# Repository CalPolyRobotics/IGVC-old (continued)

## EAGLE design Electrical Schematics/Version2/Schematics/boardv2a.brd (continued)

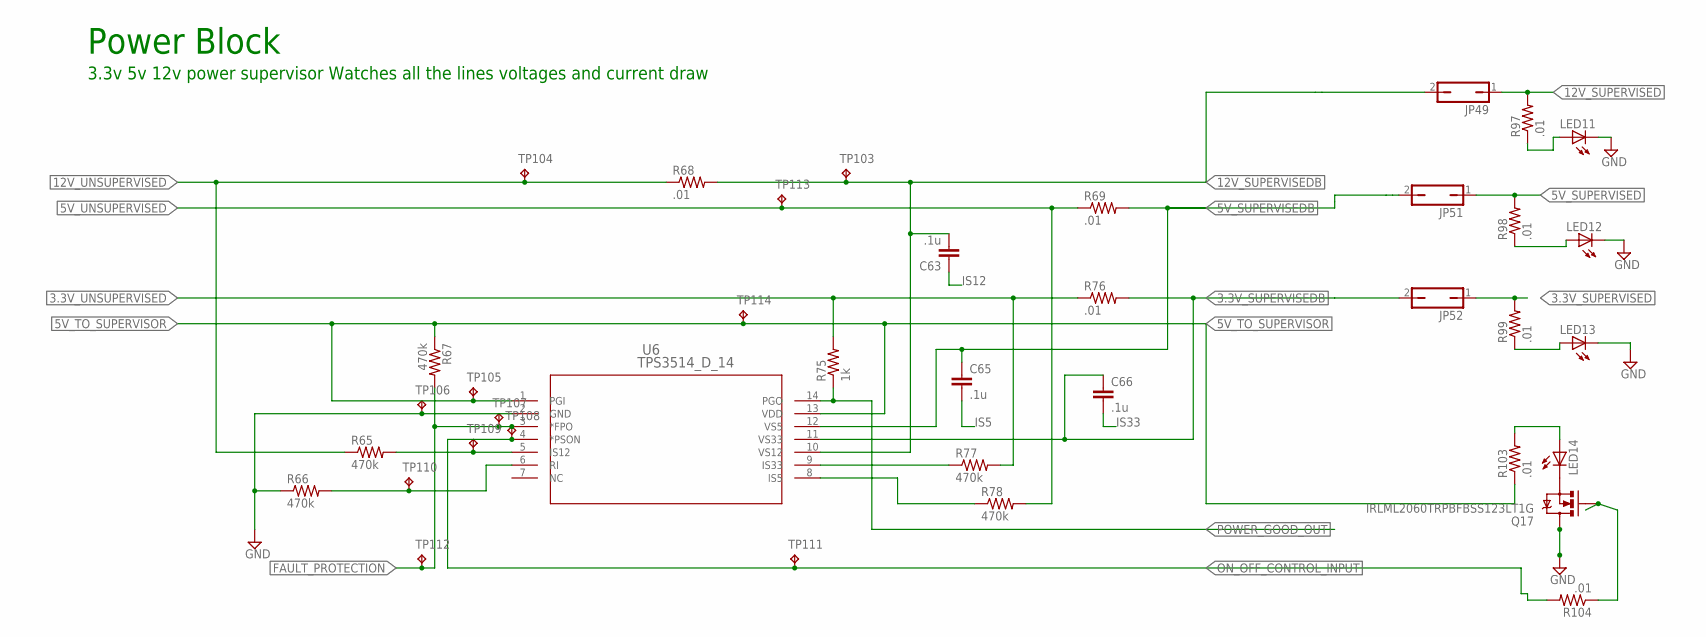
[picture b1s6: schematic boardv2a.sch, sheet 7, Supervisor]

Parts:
C63, C65, C66: .1u; C0603
JP49, JP51, JP52: JP1Q; JP1
LED11, LED12, LED13, LED14: LEDSML1206; SML1206
Q17: IRLML2060TRPBFBSS123LT1G; SOT23-3
R65, R66, R67, R77, R78: 470k; 0603-RES
R68, R69, R76, R97, R98, R99, R103, R104: .01; 0603-RES
R75: 1k; 0603-RES
TP103, TP105, TP106, TP107, TP108, TP109, TP110, TP111, TP112, TP113, TP114: TPB1,27; B1,27
TP104: TPTP06R; TP06R
U6: TPS3514_D_14; D14

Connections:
3.3V_SUPERVISED: JP52.1, R99.2; also elsewhere on the board
3.3V_SUPERVISEDB: C66.1, JP52.2, R76.2, U6.11 (VS33)
3.3V_UNSUPERVISED: R75.2, R76.1, R77.2; also elsewhere on the board
5V_SUPERVISED: JP51.1, R98.2; also elsewhere on the board
5V_SUPERVISEDB: C65.1, JP51.2, R69.2, U6.12 (VS5)
5V_TO_SUPERVISOR: R67.1, R103.1, TP105.TP, TP114.TP, U6.1 (PGI), U6.13 (VDD); also elsewhere on the board
5V_UNSUPERVISED: R69.1, R78.2, TP113.TP; also elsewhere on the board
12V_SUPERVISED: JP49.1, R97.2; also elsewhere on the board
12V_SUPERVISEDB: C63.2, JP49.2, R68.2, TP103.TP, U6.10 (VS12)
12V_UNSUPERVISED: R65.1, R68.1, TP104.TP; also elsewhere on the board
FAULT_PROTECTION: R67.2, TP107.TP, TP112.TP, U6.3 (*FPO)
GND: LED11.C, LED12.C, LED13.C, Q17.3 (D), R66.1, TP106.TP, U6.2 (GND); also elsewhere on the board
IS5: C65.2, R78.1, U6.8 (IS5)
IS12: C63.1, R65.2, TP109.TP, U6.5 (IS12)
IS33: C66.2, R77.1, U6.9 (IS33)
unnamed: LED14.C, Q17.2 (S)
unnamed: R66.2, TP110.TP, U6.6 (RI)
unnamed: LED13.A, R99.1
unnamed: LED12.A, R98.1
unnamed: LED11.A, R97.1
unnamed: LED14.A, R103.2
unnamed: Q17.1 (G), R104.1
ON_OFF_CONTROL_INPUT: R104.2, TP108.TP, TP111.TP, U6.4 (*PSON)
POWER_GOOD_OUT: R75.1, U6.14 (PGO); also elsewhere on the board

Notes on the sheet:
Power Block
3.3v 5v 12v power supervisor Watches all the lines voltages and current draw

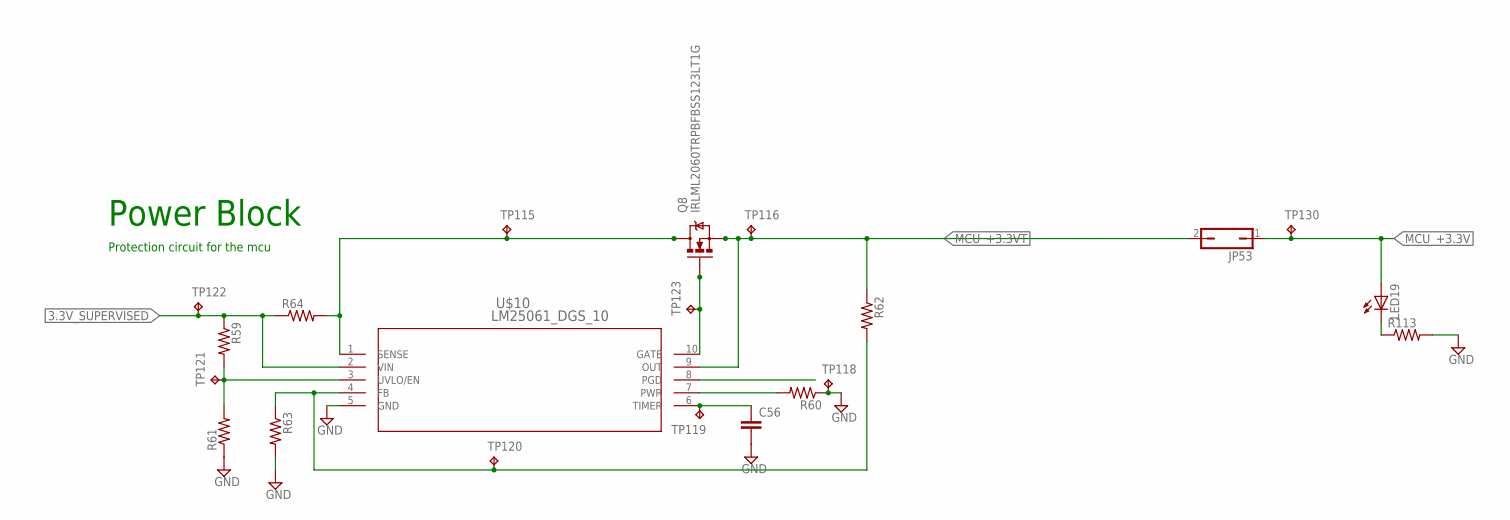
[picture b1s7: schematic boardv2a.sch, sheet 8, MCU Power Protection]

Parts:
C56: CC0603; C0603
JP53: JP1Q; JP1
LED19: LEDSML1206; SML1206
Q8: IRLML2060TRPBFBSS123LT1G; SOT23-3
R59, R60, R61, R62, R63, R64, R113: RESISTOR0603-RES; 0603-RES
TP115, TP116, TP118, TP119, TP120, TP121, TP122, TP123, TP130: TPB1,27; B1,27
U$10: LM25061_DGS_10; MUB10A

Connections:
3.3V_SUPERVISED: R59.1, R64.1, TP122.TP, U$10.2 (VIN); also elsewhere on the board
GND: C56.2, R60.1, R61.1, R63.2, R113.2, TP118.TP, U$10.5 (GND); also elsewhere on the board
MCU_+3.3V: JP53.1, LED19.A, TP130.TP; also elsewhere on the board
MCU_+3.3VT: JP53.2, Q8.2 (S), R62.1, TP116.TP, U$10.9 (OUT)
unnamed: C56.1, TP119.TP, U$10.6 (TIMER)
unnamed: R60.2, U$10.7 (PWR)
unnamed: R59.2, R61.2, TP121.TP, U$10.3 (UVLO/EN)
unnamed: Q8.3 (D), R64.2, TP115.TP, U$10.1 (SENSE)
unnamed: Q8.1 (G), TP123.TP, U$10.10 (GATE)
unnamed: R62.2, R63.1, TP120.TP, U$10.4 (FB)
unnamed: LED19.C, R113.1

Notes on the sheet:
Power Block
Protection circuit for the mcu

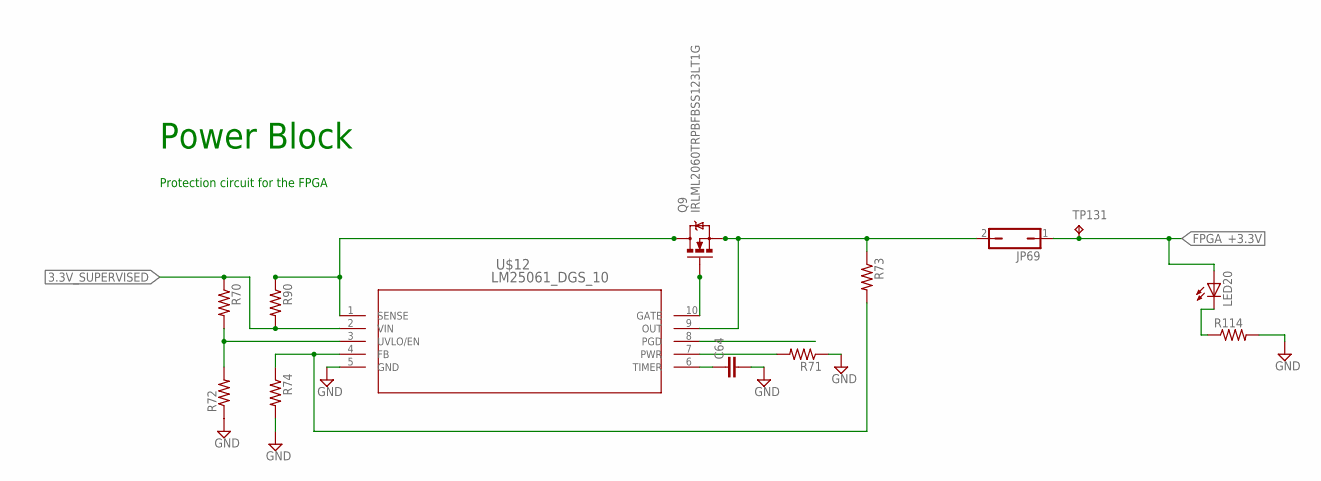
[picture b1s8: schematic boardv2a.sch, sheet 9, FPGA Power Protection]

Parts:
C64: CC0603; C0603
JP69: JP1Q; JP1
LED20: LEDSML1206; SML1206
Q9: IRLML2060TRPBFBSS123LT1G; SOT23-3
R70, R71, R72, R73, R74, R90, R114: RESISTOR0603-RES; 0603-RES
TP131: TPB1,27; B1,27
U$12: LM25061_DGS_10; MUB10A

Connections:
3.3V_SUPERVISED: R70.1, R90.2, U$12.2 (VIN); also elsewhere on the board
FPGA_+3.3V: JP69.1, LED20.A, TP131.TP
GND: C64.2, R71.1, R72.1, R74.2, R114.2, U$12.5 (GND); also elsewhere on the board
unnamed: C64.1, U$12.6 (TIMER)
unnamed: R71.2, U$12.7 (PWR)
unnamed: R70.2, R72.2, U$12.3 (UVLO/EN)
unnamed: Q9.3 (D), R90.1, U$12.1 (SENSE)
unnamed: Q9.1 (G), U$12.10 (GATE)
unnamed: R73.2, R74.1, U$12.4 (FB)
unnamed: JP69.2, Q9.2 (S), R73.1, U$12.9 (OUT)
unnamed: LED20.C, R114.1

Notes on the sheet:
Power Block
Protection circuit for the FPGA

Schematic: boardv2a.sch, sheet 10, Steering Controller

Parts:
R2401, R2402, R2403, R2404, R2405: 1k; R0603
SV2: FE05-1

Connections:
MCU_STEERCTRL_DIAGA: R2403.1; also elsewhere on the board
MCU_STEERCTRL_DIAGB: R2404.1; also elsewhere on the board
MCU_STEERCTRL_INA: R2401.1; also elsewhere on the board
MCU_STEERCTRL_INB: R2402.1; also elsewhere on the board
MCU_STEERCTRL_PWM: R2405.1; also elsewhere on the board
unnamed: R2404.2, SV2.4
unnamed: R2402.2, SV2.2
unnamed: R2403.2, SV2.3
unnamed: R2405.2, SV2.5

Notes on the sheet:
Steering Controller

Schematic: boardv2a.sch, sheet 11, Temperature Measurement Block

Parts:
JP97, JP98, JP99, JP100, JP101, JP102: JP2E; JP2

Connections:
3.3V_TEMP_PWR: JP97.2, JP98.2, JP99.2, JP100.2, JP101.2, JP102.2
MCU_A_GND: JP97.3, JP98.3, JP99.3, JP100.3, JP101.3, JP102.3; also elsewhere on the board
MCU_TEMPB_A1: JP98.1; also elsewhere on the board
MCU_TEMPC_A2: JP99.1; also elsewhere on the board
MCU_TEMPD_A3: JP100.1; also elsewhere on the board
MCU_TEMPE_A4: JP101.1; also elsewhere on the board
MCU_TEMPF_A5: JP102.1; also elsewhere on the board
MCU_TEMP_A0: JP97.1; also elsewhere on the board

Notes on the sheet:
motorcontroler
regular 3.3 temp
regulator 5v temp
regulator 12v temp
motor temp
ESC temp
Tempature Measurement Block

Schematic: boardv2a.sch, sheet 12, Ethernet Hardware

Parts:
C16, C70, C71: 0.1uF; C0603
C72, C73: 18pf; C0603
C74, C75, C77, C78, C79, C80, C81, C82, C83, C84, C85, C109, C110, C111: 0.1uf; C0603
C76: 0.1; C0603
C106: 3.3uf; C0603
C107, C108: 10uf; C0603
JP48: JP1E; JP1
L3, L4: BLM15HB121SN1; 0402
LED10: LEDSML1206; SML1206
R28: 1k; 0603-RES
R30: 10k; 0603-RES
R82, R83, R86, R87: 51; 0603-RES
R84, R85: 200; 0603-RES
R88: 16; 0603-RES
R89: 300; 0603-RES
R94: 560ohms; 0603-RES
U8: W5100; LQFP-80
U$21: 7A-16.000MAAJ-T; 2-SMD
U$22: ETHERNET_CONNECTOR; RB1-125BAG1A

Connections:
0.1: R83.2, U8.8 (TXOP), U$22.R1
1V8A: C84.1, C85.1, C108.1, L3.2, U8.7 (1V8A), U8.74 (1V8A)
1V8D: C106.1, C107.1, L3.1
3.3V_SUPERVISED: JP48.1; also elsewhere on the board
3V3A: C110.1, C111.1, L4.1, U8.2 (3V3A)
ETHERNET_3.3_J_+: C16.1, C74.1, C75.1, C76.1, C77.1, C78.1, C79.1, C109.1, JP48.2, L4.2, LED10.A, R28.1, R84.2, R85.2, U8.12 (3V3D), U8.18 (3V3D), U8.44 (3V3D), U$22.R3
ETHERNET_MCU_INT: R30.2, U8.56 (*INT); also elsewhere on the board
GND: C16.2, C70.2, C71.2, C72.2, C73.2, C74.2, C75.2, C76.2, C77.2, C78.2, C79.2, C80.2, C81.2, C82.2, C83.2, C106.2, C107.2, C109.2, R30.1, R89.1, R94.1; also elsewhere on the board
GNDA: C84.2, C85.2, C108.2, C110.2, C111.2, U8.4 (GNDA), U8.10 (GNDA), U8.77 (GNDA)
MCU_ETHERNET_MISO: U8.27 (MISO); also elsewhere on the board
MCU_ETHERNET_MOSI: U8.28 (MOSI); also elsewhere on the board
MCU_ETHERNET_SCLK: U8.30 (SCLK); also elsewhere on the board
MCU_ETHERNET_SCS: U8.29 (*SCS); also elsewhere on the board
MCU_ETHERNET_SEN: R28.2, U8.31 (SEN)
unnamed: C71.1, R82.2, R83.1
unnamed: C70.1, R86.1, R87.2
unnamed: R82.1, U8.9 (TXON), U$22.R2
unnamed: R84.1, U$22.L1
unnamed: R85.1, U$22.L3
unnamed: R87.1, U8.6 (RXIN), U$22.R7
unnamed: R86.2, U8.5 (RXIP), U$22.R8
unnamed: U8.66 (LINKLED), U$22.L2
unnamed: U8.70 (FDXLED), U$22.L4
unnamed: LED10.C, R94.2
unnamed: C80.1, C81.1, C82.1, C83.1, U8.11 (1V8OUT), U8.15 (1V8D), U8.16 (1V8D), U8.33 (1V8D), U8.69 (1V8D)
unnamed: R88.1, R89.2
unnamed: R88.2, U8.1 (RSET_BG)
P$1_CLK_TO_XTLN_WIZNET: C72.1, U8.75 (XTLN), U$21.P$1
P$2_CLK_TO_XTLP_WIZNET: C73.1, U8.76 (XTLP), U$21.P$2
WIZNET_TO_GND: U8.13 (GNDD), U8.14 (GNDD), U8.17 (GNDD), U8.32 (GNDD), U8.34 (TEST3), U8.35 (TEST2), U8.36 (TEST1), U8.37 (TEST0), U8.43 (GNDD), U8.63 (OPMODE0), U8.64 (OPMODE1), U8.65 (OPMODE2), U8.68 (GNDD)

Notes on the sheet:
Ethernet Hardware Block

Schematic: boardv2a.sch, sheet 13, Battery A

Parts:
C1: 47nF; C0603
C2: 220nF; C0603
C3: 1uF; C0603
C4: 220pf; C0603
C5: 4.7UF; C0603
J1: JU05
JP3, JP21, JP28: JP1E; JP1
JP22: JP2E; JP2
LED8: LEDSML1206; SML1206
R1: 2.2KOHM; 0603-RES
R2: 100UOHMS; 0603-RES
R9, R10: 500ohm; 0603-RES
R12: 3.3k; 0603-RES
R92: 560ohms; 0603-RES
SV3: MA03-2
U$1: MM912_637D1; QFN48
X1: KK-156-2

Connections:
5V_SUPERVISED: C5.1, JP21.1; also elsewhere on the board
BKGND: R12.1, SV3.6, U$1.47 (BKGD/MODC)
CON_MONA_+: JP3.1; also elsewhere on the board
CON_MONA_+_J: JP3.2, LED8.A, R1.2
CON_MONA_-: C2.2, C3.2, JP22.1, R2.2, R9.2, U$1.11 (VSSRX), U$1.13 (VSSD2D), U$1.18 (DGND); also elsewhere on the board
CON_MONB_+: R2.1, R10.2; also elsewhere on the board
GND: C4.2, C5.2, JP22.3, R92.1, SV3.5, U$1.4 (TEST), U$1.16 (GNDSUB), U$1.20 (GNDSUB1), U$1.30 (GNDSUB2), U$1.41 (GNDSUB3), U$1.44 (DGND1); also elsewhere on the board
MCU_BATMON_LIN: U$1.22 (LIN); also elsewhere on the board
MCU_BATMON_LINGND: U$1.23 (LGND); also elsewhere on the board
MCU_IO_RALAYA: U$1.6 (PA4); also elsewhere on the board
MONA_AGND: C1.2, JP22.2, U$1.27 (AGND), U$1.33 (ADCGND)
unnamed: R1.1, U$1.34 (VSENSE)
unnamed: J1.5, U$1.10 (PA0/MISO)
unnamed: J1.4, U$1.9 (PA1/MOSI)
unnamed: J1.3, U$1.8 (PA2/SCK)
unnamed: J1.2, U$1.7 (PA3/*SS)
unnamed: C4.1, U$1.29 (TSUP), X1.1
unnamed: U$1.28 (VTEMP), X1.2
unnamed: JP28.2, SV3.3, U$1.46 (*RESET)
unnamed: C3.1, U$1.14 (VDDD2D), U$1.19 (VDDH)
unnamed: JP28.1, U$1.45 (*RESET_A)
unnamed: R10.1, U$1.32 (ISENSEH)
unnamed: R9.1, U$1.31 (ISENSEL)
unnamed: C1.1, U$1.26 (VDDA)
unnamed: LED8.C, R92.2
VDDX: C2.1, R12.2, SV3.1, U$1.12 (VDDRX), U$1.17 (VDDX)
VSUP: JP21.2, U$1.21 (VSUP)

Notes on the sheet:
Battery Monitoring Block A
TEMP CONNECTOR

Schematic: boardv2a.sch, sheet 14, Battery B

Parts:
C6: 47nF; C0603
C7: 220nF; C0603
C8: 1uF; C0603
C9: 4.7UF; C0603
C10: 220pf; C0603
J2: JU05
JP2, JP23, JP29: JP1E; JP1
JP24: JP2E; JP2
LED7: LEDSML1206; SML1206
R3: 2.2KOHM; 0603-RES
R4: 100UOHMS; 0603-RES
R5, R6: 500ohm; 0603-RES
R22: 3.3k; 0603-RES
R36: 560ohms; 0603-RES
SV4: MA03-2
U$2: MM912_637D1; QFN48
X2: KK-156-2

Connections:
5V_SUPERVISED: C9.1, JP23.1; also elsewhere on the board
5V_SUP_J1: JP23.2, U$2.21 (VSUP)
BKGNDB: R22.1, SV4.6
CON_MONB_+: JP2.1; also elsewhere on the board
CON_MONB_+_J: JP2.2, LED7.A, R3.2
CON_MONB_-: C7.2, C8.2, JP24.1, R4.2, R5.2, U$2.11 (VSSRX), U$2.13 (VSSD2D), U$2.18 (DGND); also elsewhere on the board
CON_MONC_+: R4.1, R6.2; also elsewhere on the board
GND: C9.2, C10.2, JP24.3, R36.1, SV4.5, U$2.4 (TEST), U$2.16 (GNDSUB), U$2.20 (GNDSUB1), U$2.30 (GNDSUB2), U$2.41 (GNDSUB3), U$2.44 (DGND1); also elsewhere on the board
MCU_BATMON_LIN: U$2.22 (LIN); also elsewhere on the board
MCU_BATMON_LINGND: U$2.23 (LGND); also elsewhere on the board
MCU_IO_RALAYB: U$2.6 (PA4); also elsewhere on the board
MONB_AGND: C6.2, JP24.2, U$2.27 (AGND), U$2.33 (ADCGND)
unnamed: J2.5, U$2.10 (PA0/MISO)
unnamed: JP29.1, U$2.45 (*RESET_A)
unnamed: J2.4, U$2.9 (PA1/MOSI)
unnamed: J2.3, U$2.8 (PA2/SCK)
unnamed: J2.2, U$2.7 (PA3/*SS)
unnamed: R3.1, U$2.34 (VSENSE)
unnamed: C10.1, U$2.29 (TSUP), X2.1
unnamed: U$2.28 (VTEMP), X2.2
unnamed: JP29.2, SV4.3, U$2.46 (*RESET)
unnamed: R6.1, U$2.32 (ISENSEH)
unnamed: C6.1, U$2.26 (VDDA)
unnamed: R5.1, U$2.31 (ISENSEL)
unnamed: C8.1, U$2.14 (VDDD2D), U$2.19 (VDDH)
unnamed: LED7.C, R36.2
VDDXB: C7.1, R22.2, SV4.1, U$2.12 (VDDRX), U$2.17 (VDDX)

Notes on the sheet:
Battery Monitor B
TEMP CONNECTOR

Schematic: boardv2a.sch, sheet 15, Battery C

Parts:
C11: 47nF; C0603
C12: 220nF; C0603
C13: 1uF; C0603
C14: 4.7UF; C0603
C15: 220pf; C0603
J3: JU05
JP1, JP25, JP30: JP1E; JP1
JP26: JP2E; JP2
LED6: LEDSML1206; SML1206
R7: 2.2KOHM; 0603-RES
R8: 100UOHMS; 0603-RES
R23: 3.3k; 0603-RES
R37, R38: 500ohm; 0603-RES
R39: 560ohms; 0603-RES
SV5: MA03-2
U$3: MM912_637D1; QFN48
X3: KK-156-2

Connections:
5V_SUPERVISED: C14.1, JP25.1; also elsewhere on the board
5V_SU_J: JP25.2, U$3.21 (VSUP)
BKGNDC: R23.1, SV5.6
CON_MONC_+: JP1.1; also elsewhere on the board
CON_MONC_+_J: JP1.2, LED6.A, R7.2
CON_MONC_-: C12.2, C13.2, JP26.1, R8.2, R37.2, U$3.11 (VSSRX), U$3.13 (VSSD2D), U$3.18 (DGND); also elsewhere on the board
CON_MONC_SP: R8.1, R38.2; also elsewhere on the board
GND: C14.2, C15.2, JP26.3, R39.1, SV5.5, U$3.4 (TEST), U$3.16 (GNDSUB), U$3.20 (GNDSUB1), U$3.30 (GNDSUB2), U$3.41 (GNDSUB3), U$3.44 (DGND1); also elsewhere on the board
MCU_BATMON_LIN: U$3.22 (LIN); also elsewhere on the board
MCU_BATMON_LINGND: U$3.23 (LGND); also elsewhere on the board
MCU_IO_RALAYC: U$3.6 (PA4); also elsewhere on the board
MONC_AGND: C11.2, JP26.2, U$3.27 (AGND), U$3.33 (ADCGND)
unnamed: JP30.2, SV5.3, U$3.46 (*RESET)
unnamed: JP30.1, U$3.45 (*RESET_A)
unnamed: J3.5, U$3.10 (PA0/MISO)
unnamed: J3.4, U$3.9 (PA1/MOSI)
unnamed: J3.3, U$3.8 (PA2/SCK)
unnamed: J3.2, U$3.7 (PA3/*SS)
unnamed: R7.1, U$3.34 (VSENSE)
unnamed: C12.1, U$3.12 (VDDRX), U$3.17 (VDDX)
unnamed: C15.1, U$3.29 (TSUP), X3.1
unnamed: U$3.28 (VTEMP), X3.2
unnamed: R38.1, U$3.32 (ISENSEH)
unnamed: C11.1, U$3.26 (VDDA)
unnamed: R37.1, U$3.31 (ISENSEL)
unnamed: LED6.C, R39.2
VDDXC: C13.1, R23.2, SV5.1, U$3.14 (VDDD2D), U$3.19 (VDDH)

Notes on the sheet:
Battery Monitoring Block C
TEMP CONNECTOR

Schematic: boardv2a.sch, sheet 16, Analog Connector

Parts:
JP111: JP2E; JP2

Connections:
MCU_+3.3V: JP111.3; also elsewhere on the board
MCU_A_GND: JP111.1; also elsewhere on the board
MCU_STEERING_POT: JP111.2; also elsewhere on the board

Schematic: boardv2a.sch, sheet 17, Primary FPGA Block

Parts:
C21, C22, C23, C25, C26, C27, C28, C88: 10uF; 0603-CAP
C24, C29, C30, C31, C32, C33, C34, C35, C36, C37, C89: 1uF; 0603-CAP
L7: BLM15HB121SN1; 0402
Q7: ASFL1; ASF
R33: 10k; 0603-RES
U$6: XC6SLX4-2TQG144C; TQ144
U$11: 1.2VREG; SOT-223

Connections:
128MHZCLK_OUT_TO_GCLK_FPGA: Q7.3 (FO), U$6.P56 (IO_L30P_GCLK1_D13_2)
CONGND: L7.2; also elsewhere on the board
FPGA_CMPCS_B_2: U$6.P72 (CMPCS_B_2)
FPGA_DONE_2: U$6.P71 (DONE_2)
FPGA_L1N_1: U$6.P104 (IO_L1N_VREF_1); also elsewhere on the board
FPGA_L1N_2: U$6.P69 (IO_L1N_M0_CMPMISO_2); also elsewhere on the board
FPGA_L1N_3_MODULEF_ISOLATOR: U$6.P34 (IO_L1N_VREF_3); also elsewhere on the board
FPGA_L1P_1: U$6.P105 (IO_L1P_1); also elsewhere on the board
FPGA_L1P_2: U$6.P70 (IO_L1P_CCLK_2); also elsewhere on the board
FPGA_L1P_3_MODULEF_ISOLATOR: U$6.P35 (IO_L1P_3); also elsewhere on the board
FPGA_L2N_2: U$6.P66 (IO_L2N_CMPMOSI_2); also elsewhere on the board
FPGA_L2N_3: U$6.P32 (IO_L2N_3); also elsewhere on the board
FPGA_L2P_2: U$6.P67 (IO_L2P_CMPCLK_2); also elsewhere on the board
FPGA_L2P_3: U$6.P33 (IO_L2P_3); also elsewhere on the board
FPGA_L3N_0: U$6.P139 (IO_L3N_0); also elsewhere on the board
FPGA_L3N_2: U$6.P64 (IO_L3N_MOSI_CSI_B_MISO0_2); also elsewhere on the board
FPGA_L3P_0: U$6.P140 (IO_L3P_0); also elsewhere on the board
FPGA_L3P_2: U$6.P65 (IO_L3P_D0_DIN_MISO_MISO1_2); also elsewhere on the board
FPGA_L12N_2: U$6.P61 (IO_L12N_D2_MISO3_2); also elsewhere on the board
FPGA_L12P_2: U$6.P62 (IO_L12P_D1_MISO2_2); also elsewhere on the board
FPGA_L13N_2: U$6.P59 (IO_L13N_D10_2); also elsewhere on the board
FPGA_L13P_2: U$6.P60 (IO_L13P_M1_2); also elsewhere on the board
FPGA_L14N_2_MODULEG_ISOLATOR: U$6.P57 (IO_L14N_D12_2); also elsewhere on the board
FPGA_L14P_2_MODULEG_ISOLATOR: U$6.P58 (IO_L14P_D11_2); also elsewhere on the board
FPGA_L30N_2: U$6.P55 (IO_L30N_GCLK0_USERCCLK_2); also elsewhere on the board
FPGA_L31N_2: U$6.P50 (IO_L31N_GCLK30_D15_2); also elsewhere on the board
FPGA_L31P_2: U$6.P51 (IO_L31P_GCLK31_D14_2); also elsewhere on the board
FPGA_L32N_1: U$6.P101 (IO_L32N_1); also elsewhere on the board
FPGA_L32P_1: U$6.P102 (IO_L32P_1); also elsewhere on the board
FPGA_L33N_1: U$6.P99 (IO_L33N_1); also elsewhere on the board
FPGA_L33P_1: U$6.P100 (IO_L33P_1); also elsewhere on the board
FPGA_L34N_1: U$6.P97 (IO_L34N_1); also elsewhere on the board
FPGA_L34P_1: U$6.P98 (IO_L34P_1); also elsewhere on the board
FPGA_L36N_3_MODULEC_ISOLATOR: U$6.P29 (IO_L36N_3); also elsewhere on the board
FPGA_L36P_3_MODULEC_ISOLATOR: U$6.P30 (IO_L36P_3); also elsewhere on the board
FPGA_L37N_3: U$6.P26 (IO_L37N_3); also elsewhere on the board
FPGA_L37P_3: U$6.P27 (IO_L37P_3); also elsewhere on the board
FPGA_L40N_1: U$6.P94 (IO_L40N_GCLK10_1); also elsewhere on the board
FPGA_L40P_1: U$6.P95 (IO_L40P_GCLK11_1); also elsewhere on the board
FPGA_L41N_1: U$6.P92 (IO_L41N_GCLK8_1); also elsewhere on the board
FPGA_L41N_3: U$6.P23 (IO_L41N_GCLK26_3); also elsewhere on the board
FPGA_L41P_1: U$6.P93 (IO_L41P_GCLK9_IRDY1_1); also elsewhere on the board
FPGA_L41P_3: U$6.P24 (IO_L41P_GCLK27_3); also elsewhere on the board
FPGA_L42N_3: U$6.P21 (IO_L42N_GCLK24_3); also elsewhere on the board
FPGA_L42N_GCLK6_TRDY1_1: U$6.P87 (IO_L42N_GCLK6_TRDY1_1); also elsewhere on the board
FPGA_L42P_1: U$6.P88 (IO_L42P_GCLK7_1); also elsewhere on the board
FPGA_L42P_3: U$6.P22 (IO_L42P_GCLK25_TRDY2_3); also elsewhere on the board
FPGA_L43N_1: U$6.P84 (IO_L43N_GCLK4_1); also elsewhere on the board
FPGA_L43N_3: U$6.P16 (IO_L43N_GCLK22_IRDY2_3); also elsewhere on the board
FPGA_L43P_1: U$6.P85 (IO_L43P_GCLK5_1); also elsewhere on the board
FPGA_L43P_3: U$6.P17 (IO_L43P_GCLK23_3); also elsewhere on the board
FPGA_L44N_3: U$6.P14 (IO_L44N_GCLK20_3); also elsewhere on the board
FPGA_L44P_3: U$6.P15 (IO_L44P_GCLK21_3); also elsewhere on the board
FPGA_L45N_1: U$6.P82 (IO_L45N_1); also elsewhere on the board
FPGA_L45P_1: U$6.P83 (IO_L45P_1); also elsewhere on the board
FPGA_L46N_1_MODULEA_ISOLATOR: U$6.P80 (IO_L46N_1); also elsewhere on the board
FPGA_L46P_1_MODULEA_ISOLATOR: U$6.P81 (IO_L46P_1); also elsewhere on the board
FPGA_L47N_1_MODULEH_ISOLATOR: U$6.P78 (IO_L47N_1); also elsewhere on the board
FPGA_L47P_1_MODULEH_ISOLATOR: U$6.P79 (IO_L47P_1); also elsewhere on the board
FPGA_L48N_2: U$6.P47 (IO_L48N_RDWR_B_VREF_2); also elsewhere on the board
FPGA_L48P_2: U$6.P48 (IO_L48P_D7_2); also elsewhere on the board
FPGA_L49N_2: U$6.P45 (IO_L49N_D4_2); also elsewhere on the board
FPGA_L49N_3: U$6.P11 (IO_L49N_3); also elsewhere on the board
FPGA_L49P_2: U$6.P46 (IO_L49P_D3_2); also elsewhere on the board
FPGA_L49P_3: U$6.P12 (IO_L49P_3); also elsewhere on the board
FPGA_L50N_3: U$6.P9 (IO_L50N_3); also elsewhere on the board
FPGA_L50P_3: U$6.P10 (IO_L50P_3); also elsewhere on the board
FPGA_L51N_3: U$6.P7 (IO_L51N_3); also elsewhere on the board
FPGA_L51P_3: U$6.P8 (IO_L51P_3); also elsewhere on the board
FPGA_L52N_3: U$6.P5 (IO_L52N_3); also elsewhere on the board
FPGA_L52P_3: U$6.P6 (IO_L52P_3); also elsewhere on the board
FPGA_L62N_0: U$6.P120 (IO_L62N_VREF_0); also elsewhere on the board
FPGA_L62N_2: U$6.P43 (IO_L62N_D6_2); also elsewhere on the board
FPGA_L62P_2: U$6.P44 (IO_L62P_D5_2); also elsewhere on the board
FPGA_L63N_0: U$6.P118 (IO_L63N_SCP6_0); also elsewhere on the board
FPGA_L63P_0: U$6.P119 (IO_L63P_SCP7_0); also elsewhere on the board
FPGA_L64N_0: U$6.P116 (IO_L64N_SCP4_0); also elsewhere on the board
FPGA_L64N_2: U$6.P40 (IO_L64N_D9_2); also elsewhere on the board
FPGA_L64P_0: U$6.P117 (IO_L64P_SCP5_0); also elsewhere on the board
FPGA_L64P_2: U$6.P41 (IO_L64P_D8_2); also elsewhere on the board
FPGA_L65N_0: U$6.P114 (IO_L65N_SCP2_0); also elsewhere on the board
FPGA_L65N_2_MODULEE_ISOLATOR: U$6.P38 (IO_L65N_CSO_B_2); also elsewhere on the board
FPGA_L65P_0: U$6.P115 (IO_L65P_SCP3_0); also elsewhere on the board
FPGA_L65P_2_MODULEE_ISOLATOR: U$6.P39 (IO_L65P_INIT_B_2); also elsewhere on the board
FPGA_L66N_0: U$6.P111 (IO_L66N_SCP0_0); also elsewhere on the board
FPGA_L66P_0: U$6.P112 (IO_L66P_SCP1_0); also elsewhere on the board
FPGA_L74N_1_MODULEB_ISOLATOR: U$6.P74 (IO_L74N_DOUT_BUSY_1); also elsewhere on the board
FPGA_L74P_1_MODULEB_ISOLATOR: U$6.P75 (IO_L74P_AWAKE_1); also elsewhere on the board
FPGA_L83N_3_MODULED_ISOLATOR: U$6.P1 (IO_L83N_VREF_3); also elsewhere on the board
FPGA_L83P_3_MODULED_ISOLATOR: U$6.P2 (IO_L83P_3); also elsewhere on the board
FPGA_MCU_AD1: U$6.P123 (IO_L37N_GCLK12_0); also elsewhere on the board
FPGA_MCU_AD2: U$6.P124 (IO_L37P_GCLK13_0); also elsewhere on the board
FPGA_MCU_AD3: U$6.P126 (IO_L36N_GCLK14_0); also elsewhere on the board
FPGA_MCU_AD4: U$6.P127 (IO_L36P_GCLK15_0); also elsewhere on the board
FPGA_MCU_AD5: U$6.P131 (IO_L35N_GCLK16_0); also elsewhere on the board
FPGA_MCU_AD6: U$6.P132 (IO_L35P_GCLK17_0); also elsewhere on the board
FPGA_MCU_AD7: U$6.P133 (IO_L34N_GCLK18_0); also elsewhere on the board
FPGA_MCU_ADO: U$6.P121 (IO_L62P_0); also elsewhere on the board
FPGA_MCU_CLK: U$6.P137 (IO_L4N_0); also elsewhere on the board
FPGA_MCU_RES1: U$6.P144 (IO_L1P_HSWAPEN_0); also elsewhere on the board
FPGA_MCU_RES2: U$6.P143 (IO_L1N_VREF_0); also elsewhere on the board
FPGA_MCU_RES3: U$6.P142 (IO_L2P_0); also elsewhere on the board
FPGA_MCU_RES4: U$6.P141 (IO_L2N_0); also elsewhere on the board
FPGA_MCU_RW: U$6.P134 (IO_L34P_GCLK19_0); also elsewhere on the board
FPGA_MCU_STAT: U$6.P138 (IO_L4P_0); also elsewhere on the board
FPGA_PROGRAM_B_2: U$6.P37 (PROGRAM_B_2)
FPGA_SUSPEND: R33.1, U$6.P73 (SUSPEND)
GND: C21.2, C22.2, C23.2, C24.2, C25.2, C26.2, C27.2, C28.2, C29.2, C30.2, C31.2, C32.2, C33.2, C34.2, C35.2, C36.2, C37.2, C88.2, C89.2, L7.1, Q7.2 (GND), R33.2, U$6.P3 (GND), U$6.P13 (GND), U$6.P25 (GND), U$6.P49 (GND), U$6.P54 (GND), U$6.P68 (GND), U$6.P77 (GND), U$6.P91 (GND), U$6.P96 (GND), U$6.P108 (GND), U$6.P113 (GND), U$6.P130 (GND), U$6.P136 (GND), U$11.1 (GND); also elsewhere on the board
PP_3.3V_FPGA: C25.1, C26.1, C27.1, C28.1, C29.1, C30.1, C31.1, C32.1, C33.1, C34.1, C35.1, C36.1, C37.1, C89.1, Q7.1 (OE), Q7.4 (VCC), U$6.P4 (VCCO_3), U$6.P18 (VCCO_3), U$6.P20 (VCCAUX), U$6.P31 (VCCO_3), U$6.P36 (VCCAUX), U$6.P42 (VCCO_2), U$6.P53 (VCCAUX), U$6.P63 (VCCO_2), U$6.P76 (VCCO_1), U$6.P86 (VCCO_1), U$6.P90 (VCCAUX), U$6.P103 (VCCO_1), U$6.P122 (VCCO_0), U$6.P125 (VCCO_0), U$6.P129 (VCCAUX), U$6.P135 (VCCO_0), U$11.3 (VIN)
TCK: U$6.P109 (TCK); also elsewhere on the board
TDI: U$6.P110 (TDI); also elsewhere on the board
TDO: U$6.P106 (TDO); also elsewhere on the board
TMS: U$6.P107 (TMS); also elsewhere on the board
VCCINT: C21.1, C22.1, C23.1, C24.1, C88.1, U$6.P19 (VCCINT), U$6.P28 (VCCINT), U$6.P52 (VCCINT), U$6.P89 (VCCINT), U$6.P128 (VCCINT), U$11.2 (VOUT), U$11.4 (TAB)

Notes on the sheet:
FPGA Block
Primary FPGA

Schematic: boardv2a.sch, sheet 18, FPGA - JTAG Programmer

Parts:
U$7: JTAG14PIN

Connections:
GND: U$7.P$8, U$7.P$9, U$7.P$10, U$7.P$11, U$7.P$12, U$7.P$13, U$7.P$14; also elsewhere on the board
HALT: U$7.P$7
TCK: U$7.P$3; also elsewhere on the board
TDI: U$7.P$5; also elsewhere on the board
TDO: U$7.P$4; also elsewhere on the board
TMS: U$7.P$2; also elsewhere on the board
VREF: U$7.P$1

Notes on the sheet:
FPGA Block
JTAG Programmer

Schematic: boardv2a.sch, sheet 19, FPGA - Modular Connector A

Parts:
C90, C91: .1uF; 0603-CAP
JP5: JP2E; JP2
U9: ADUM3442CRWZ; RW_16
U$13, U$14: DPDTSWITCH; JS202011
X5: KK-156-4

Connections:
3.3V_SUPERVISED: C91.1, U9.1 (VDD1), U9.7 (VE1); also elsewhere on the board
CONGND: C90.2, U9.9 (GND2_2), U9.15 (GND2), X5.4; also elsewhere on the board
FPGA_L46N_1_MODULEA_ISOLATOR: U$13.5 (COM2); also elsewhere on the board
FPGA_L46P_1_MODULEA_ISOLATOR: U$14.5 (COM2); also elsewhere on the board
GND: C91.2, U9.2 (GND1_2), U9.8 (GND1); also elsewhere on the board
unnamed: U$14.2 (COM1), X5.2
unnamed: U$13.2 (COM1), X5.3
unnamed: U9.14 (VOA), U$14.1
unnamed: U9.12 (VIC), U$14.3
unnamed: U9.11 (VID), U$13.3
PP_3.3V_MODULARCONNECTOR: JP5.3; also elsewhere on the board
PP_5V_MODULARCONNECTOR: JP5.1; also elsewhere on the board
V1: C90.1, JP5.2, U9.10 (VE2), U9.16 (VDD2), X5.1
VIAA: U9.3 (VIA), U$14.4
VIBA: U9.4 (VIB), U$13.4
VOBA: U9.13 (VOB), U$13.1
VOCA: U9.5 (VOC), U$14.6
VODA: U9.6 (VOD), U$13.6

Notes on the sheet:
FPGA Block
Modular Connector A With Isolation

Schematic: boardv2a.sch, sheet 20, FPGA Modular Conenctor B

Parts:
C92, C93: .1uF; 0603-CAP
JP6: JP2E; JP2
U11: ADUM3442CRWZ; RW_16
U$16, U$17: DPDTSWITCH; JS202011
X6: KK-156-4

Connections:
3.3V_SUPERVISED: C93.1, U11.1 (VDD1), U11.7 (VE1); also elsewhere on the board
CONGND: C92.2, U11.9 (GND2_2), U11.15 (GND2), X6.4; also elsewhere on the board
FPGA_L74N_1_MODULEB_ISOLATOR: U$16.5 (COM2); also elsewhere on the board
FPGA_L74P_1_MODULEB_ISOLATOR: U$17.5 (COM2); also elsewhere on the board
GND: C93.2, U11.2 (GND1_2), U11.8 (GND1); also elsewhere on the board
unnamed: U$17.2 (COM1), X6.2
unnamed: U$16.2 (COM1), X6.3
unnamed: U11.14 (VOA), U$17.1
unnamed: U11.12 (VIC), U$17.3
unnamed: U11.11 (VID), U$16.3
PP_3.3V_MODULARCONNECTOR: JP6.3; also elsewhere on the board
PP_5V_MODULARCONNECTOR: JP6.1; also elsewhere on the board
V2: C92.1, JP6.2, U11.10 (VE2), U11.16 (VDD2), X6.1
VIAB: U11.3 (VIA), U$17.4
VIBB: U11.4 (VIB), U$16.4
VOBB: U11.13 (VOB), U$16.1
VOCB: U11.5 (VOC), U$17.6
VODB: U11.6 (VOD), U$16.6

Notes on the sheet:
FPGA Block
Modular Connector B With Isolation

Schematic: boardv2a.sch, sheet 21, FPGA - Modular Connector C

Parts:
C94, C95: .1uF; 0603-CAP
JP7: JP2E; JP2
U12: ADUM3442CRWZ; RW_16
U$18, U$19: DPDTSWITCH; JS202011
X7: KK-156-4

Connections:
3.3V_SUPERVISED: C95.1, U12.1 (VDD1), U12.7 (VE1); also elsewhere on the board
CONGND: C94.2, U12.9 (GND2_2), U12.15 (GND2), X7.4; also elsewhere on the board
FPGA_L36N_3_MODULEC_ISOLATOR: U$19.5 (COM2); also elsewhere on the board
FPGA_L36P_3_MODULEC_ISOLATOR: U$18.5 (COM2); also elsewhere on the board
GND: C95.2, U12.2 (GND1_2), U12.8 (GND1); also elsewhere on the board
unnamed: U$19.2 (COM1), X7.2
unnamed: U$18.2 (COM1), X7.3
unnamed: U12.14 (VOA), U$19.1
unnamed: U12.12 (VIC), U$19.3
unnamed: U12.11 (VID), U$18.3
PP_3.3V_MODULARCONNECTOR: JP7.3; also elsewhere on the board
PP_5V_MODULARCONNECTOR: JP7.1; also elsewhere on the board
V3: C94.1, JP7.2, U12.10 (VE2), U12.16 (VDD2), X7.1
VIAC: U12.3 (VIA), U$19.4
VIBC: U12.4 (VIB), U$18.4
VOBC: U12.13 (VOB), U$18.1
VOCC: U12.5 (VOC), U$19.6
VODC: U12.6 (VOD), U$18.6

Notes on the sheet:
FPGA Block
Modular Connector C With Isolation

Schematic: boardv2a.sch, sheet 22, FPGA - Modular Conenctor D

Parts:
C96, C97: .1uF; 0603-CAP
JP8: JP2E; JP2
U13: ADUM3442CRWZ; RW_16
U$20, U$23: DPDTSWITCH; JS202011
X8: KK-156-4

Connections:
3.3V_SUPERVISED: C97.1, U13.1 (VDD1), U13.7 (VE1); also elsewhere on the board
CONGND: C96.2, U13.9 (GND2_2), U13.15 (GND2), X8.4; also elsewhere on the board
FPGA_L83N_3_MODULED_ISOLATOR: U$23.5 (COM2); also elsewhere on the board
FPGA_L83P_3_MODULED_ISOLATOR: U$20.5 (COM2); also elsewhere on the board
GND: C97.2, U13.2 (GND1_2), U13.8 (GND1); also elsewhere on the board
unnamed: U$23.2 (COM1), X8.2
unnamed: U$20.2 (COM1), X8.3
unnamed: U13.14 (VOA), U$23.1
unnamed: U13.12 (VIC), U$23.3
unnamed: U13.11 (VID), U$20.3
PP_3.3V_MODULARCONNECTOR: JP8.3; also elsewhere on the board
PP_5V_MODULARCONNECTOR: JP8.1; also elsewhere on the board
V4: C96.1, JP8.2, U13.10 (VE2), U13.16 (VDD2), X8.1
VIAD: U13.3 (VIA), U$23.4
VIBD: U13.4 (VIB), U$20.4
VOBD: U13.13 (VOB), U$20.1
VOCD: U13.5 (VOC), U$23.6
VODD: U13.6 (VOD), U$20.6

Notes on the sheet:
FPGA Block
Modular Connector D With Isolation

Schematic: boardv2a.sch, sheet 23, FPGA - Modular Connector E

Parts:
C98, C99: .1uF; 0603-CAP
JP9: JP2E; JP2
U14: ADUM3442CRWZ; RW_16
U$24, U$25: DPDTSWITCH; JS202011
X9: KK-156-4

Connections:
3.3V_SUPERVISED: C99.1, U14.1 (VDD1), U14.7 (VE1); also elsewhere on the board
CONGND: C98.2, U14.9 (GND2_2), U14.15 (GND2), X9.4; also elsewhere on the board
FPGA_L65N_2_MODULEE_ISOLATOR: U$24.5 (COM2); also elsewhere on the board
FPGA_L65P_2_MODULEE_ISOLATOR: U$25.5 (COM2); also elsewhere on the board
GND: C99.2, U14.2 (GND1_2), U14.8 (GND1); also elsewhere on the board
unnamed: U$25.2 (COM1), X9.2
unnamed: U$24.2 (COM1), X9.3
unnamed: U14.14 (VOA), U$25.1
unnamed: U14.12 (VIC), U$25.3
unnamed: U14.11 (VID), U$24.3
PP_3.3V_MODULARCONNECTOR: JP9.3; also elsewhere on the board
PP_5V_MODULARCONNECTOR: JP9.1; also elsewhere on the board
V5: C98.1, JP9.2, U14.10 (VE2), U14.16 (VDD2), X9.1
VIAE: U14.3 (VIA), U$25.4
VIBE: U14.4 (VIB), U$24.4
VOBE: U14.13 (VOB), U$24.1
VOCE: U14.5 (VOC), U$25.6
VODE: U14.6 (VOD), U$24.6

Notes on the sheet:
FPGA Block
Modular Connector E With Isolation

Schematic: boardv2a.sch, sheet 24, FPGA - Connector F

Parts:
C100, C101: .1uF; 0603-CAP
JP10: JP2E; JP2
U15: ADUM3442CRWZ; RW_16
U$26, U$27: DPDTSWITCH; JS202011
X10: KK-156-4

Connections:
3.3V_SUPERVISED: C101.1, U15.1 (VDD1), U15.7 (VE1); also elsewhere on the board
CONGND: C100.2, U15.9 (GND2_2), U15.15 (GND2), X10.4; also elsewhere on the board
FPGA_L1N_3_MODULEF_ISOLATOR: U$27.5 (COM2); also elsewhere on the board
FPGA_L1P_3_MODULEF_ISOLATOR: U$26.5 (COM2); also elsewhere on the board
GND: C101.2, U15.2 (GND1_2), U15.8 (GND1); also elsewhere on the board
unnamed: U$27.2 (COM1), X10.2
unnamed: U$26.2 (COM1), X10.3
unnamed: U15.14 (VOA), U$27.1
unnamed: U15.12 (VIC), U$27.3
unnamed: U15.11 (VID), U$26.3
PP_3.3V_MODULARCONNECTOR: JP10.3; also elsewhere on the board
PP_5V_MODULARCONNECTOR: JP10.1; also elsewhere on the board
V6: C100.1, JP10.2, U15.10 (VE2), U15.16 (VDD2), X10.1
VIAF: U15.3 (VIA), U$27.4
VIBF: U15.4 (VIB), U$26.4
VOBF: U15.13 (VOB), U$26.1
VOCF: U15.5 (VOC), U$27.6
VODF: U15.6 (VOD), U$26.6

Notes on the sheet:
FPGA Block
Modular Connector F With Isolation

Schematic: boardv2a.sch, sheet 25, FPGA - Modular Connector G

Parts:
C102, C103: .1uF; 0603-CAP
JP11: JP2E; JP2
U16: ADUM3442CRWZ; RW_16
U$28, U$29: DPDTSWITCH; JS202011
X11: KK-156-4

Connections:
3.3V_SUPERVISED: C103.1, U16.1 (VDD1), U16.7 (VE1); also elsewhere on the board
CONGND: C102.2, U16.9 (GND2_2), U16.15 (GND2), X11.4; also elsewhere on the board
FPGA_L14N_2_MODULEG_ISOLATOR: U$28.5 (COM2); also elsewhere on the board
FPGA_L14P_2_MODULEG_ISOLATOR: U$29.5 (COM2); also elsewhere on the board
GND: C103.2, U16.2 (GND1_2), U16.8 (GND1); also elsewhere on the board
unnamed: U$29.2 (COM1), X11.2
unnamed: U$28.2 (COM1), X11.3
unnamed: U16.14 (VOA), U$29.1
unnamed: U16.12 (VIC), U$29.3
unnamed: U16.11 (VID), U$28.3
PP_3.3V_MODULARCONNECTOR: JP11.3; also elsewhere on the board
PP_5V_MODULARCONNECTOR: JP11.1; also elsewhere on the board
V7: C102.1, JP11.2, U16.10 (VE2), U16.16 (VDD2), X11.1
VIAG: U16.3 (VIA), U$29.4
VIBG: U16.4 (VIB), U$28.4
VOBG: U16.13 (VOB), U$28.1
VOCG: U16.5 (VOC), U$29.6
VODG: U16.6 (VOD), U$28.6

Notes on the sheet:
FPGA Block
Modular Connector G With Isolation

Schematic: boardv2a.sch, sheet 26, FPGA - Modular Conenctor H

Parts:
C104, C105: .1uF; 0603-CAP
JP12: JP2E; JP2
U17: ADUM3442CRWZ; RW_16
U$30, U$31: DPDTSWITCH; JS202011
X12: KK-156-4

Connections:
3.3V_SUPERVISED: C105.1, U17.1 (VDD1), U17.7 (VE1); also elsewhere on the board
CONGND: C104.2, U17.9 (GND2_2), U17.15 (GND2), X12.4; also elsewhere on the board
FPGA_L47N_1_MODULEH_ISOLATOR: U$30.5 (COM2); also elsewhere on the board
FPGA_L47P_1_MODULEH_ISOLATOR: U$31.5 (COM2); also elsewhere on the board
GND: C105.2, U17.2 (GND1_2), U17.8 (GND1); also elsewhere on the board
unnamed: U$31.2 (COM1), X12.2
unnamed: U$30.2 (COM1), X12.3
unnamed: U17.14 (VOA), U$31.1
unnamed: U17.12 (VIC), U$31.3
unnamed: U17.11 (VID), U$30.3
PP_3.3V_MODULARCONNECTOR: JP12.3; also elsewhere on the board
PP_5V_MODULARCONNECTOR: JP12.1; also elsewhere on the board
V8: C104.1, JP12.2, U17.10 (VE2), U17.16 (VDD2), X12.1
VIAH: U17.3 (VIA), U$31.4
VIBH: U17.4 (VIB), U$30.4
VOBH: U17.13 (VOB), U$30.1
VOCH: U17.5 (VOC), U$31.6
VODH: U17.6 (VOD), U$30.6

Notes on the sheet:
FPGA Block
Modular Connector H With Isolation
